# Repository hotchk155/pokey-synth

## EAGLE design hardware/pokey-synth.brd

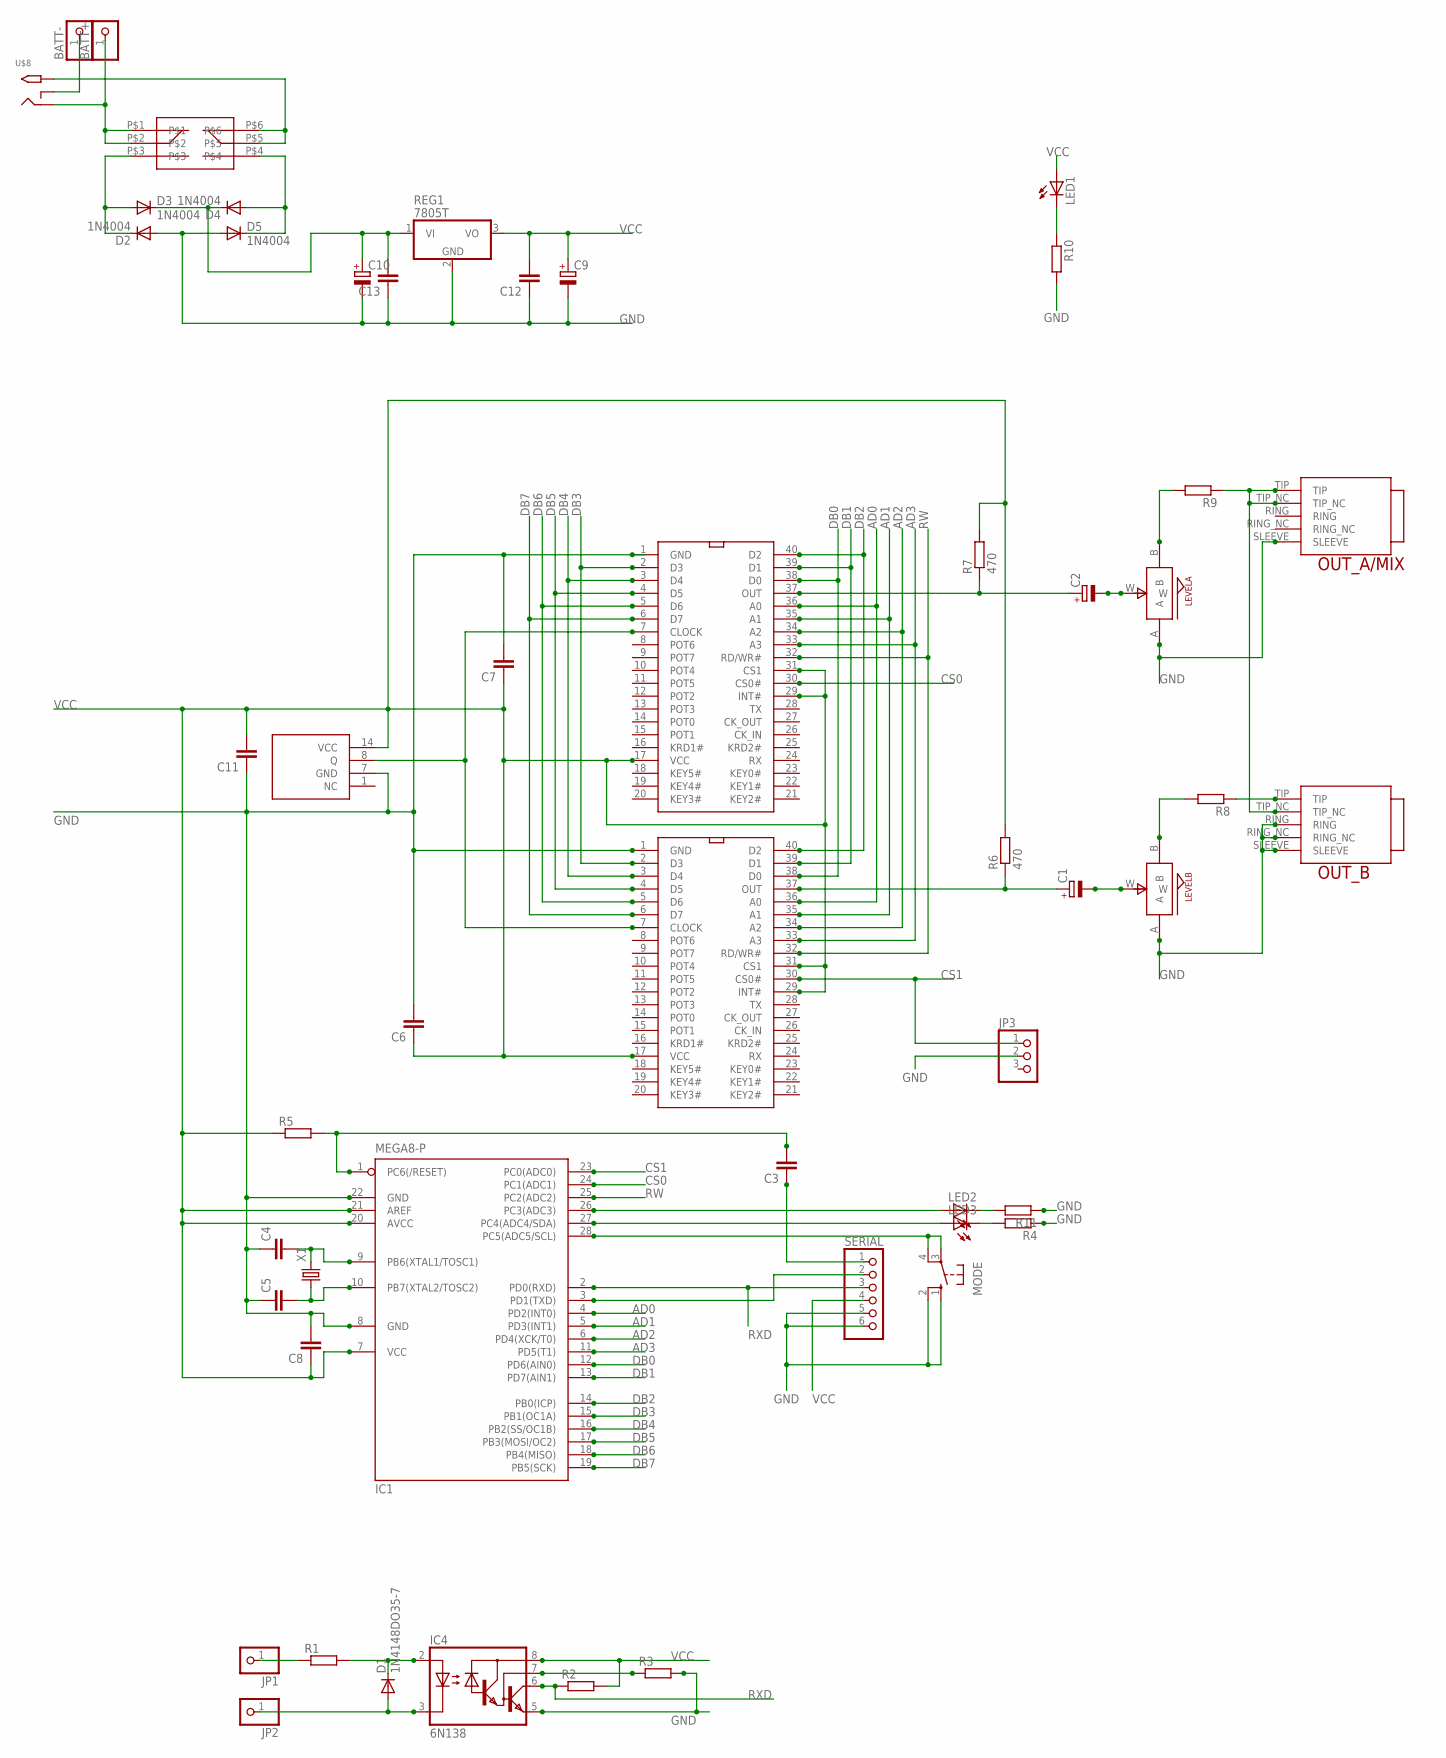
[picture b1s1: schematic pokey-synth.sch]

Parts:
BATT+: PINHD-1X1; 1X01
BATT-: PINHD-1X1; 1X01
C1, C2, C9, C10: CPOL-EUE2-5; E2-5
C3, C4, C5, C6, C7, C8, C11, C12, C13: C-EU025-024X044; C025-024X044
D1: 1N4148DO35-7; DO35-7
D2, D3, D4, D5: 1N4004; DO-VERT
IC1: MEGA8-P; DIL28-3
IC2, IC3: POKEYDIP40; DIL40
IC4: 6N138; DIL08
JP1, JP2: PINHD-1X1; 1X01
JP3: PINHD-1X3; 1X03
LED1, LED2, LED3: LED3MM
LEVELA: ALPS_POT_SMALL; SMALL_ALPS_POT
LEVELB: ALPS_POT_SMALL; SMALL_ALPS_POT
MODE: 10-XX; B3F-10XX
OSC1: TTLOSC
OUT_A/MIX: TRUCONNECTJACK
OUT_B: TRUCONNECTJACK
R1, R2, R3, R4, R5, R8, R9, R10, R11: R-EU_0207/7; 0207/7
R6, R7: 470; 0207/7
REG1: 7805T; TO220H
SERIAL: HEADER-1X6; 1X06_OVAL
U$8: 2.1MMJACKTHM; PJ-102A
U$9: 2P2T_LATCHING
X1: CRYSTALHC49U-V; HC49U-V

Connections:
AD0: IC1.4 (PD2(INT0)), IC2.36 (A0), IC3.36 (A0)
AD1: IC1.5 (PD3(INT1)), IC2.35 (A1), IC3.35 (A1)
AD2: IC1.6 (PD4(XCK/T0)), IC2.34 (A2), IC3.34 (A2)
AD3: IC1.11 (PD5(T1)), IC2.33 (A3), IC3.33 (A3)
CS0: IC1.24 (PC1(ADC1)), IC2.30 (CS0#)
CS1: IC1.23 (PC0(ADC0)), IC3.30 (CS0#), JP3.1
DB0: IC1.12 (PD6(AIN0)), IC2.38 (D0), IC3.38 (D0)
DB1: IC1.13 (PD7(AIN1)), IC2.39 (D1), IC3.39 (D1)
DB2: IC1.14 (PB0(ICP)), IC2.40 (D2), IC3.40 (D2)
DB3: IC1.15 (PB1(OC1A)), IC2.2 (D3), IC3.2 (D3)
DB4: IC1.16 (PB2(SS/OC1B)), IC2.3 (D4), IC3.3 (D4)
DB5: IC1.17 (PB3(MOSI/OC2)), IC2.4 (D5), IC3.4 (D5)
DB6: IC1.18 (PB4(MISO)), IC2.5 (D6), IC3.5 (D6)
DB7: IC1.19 (PB5(SCK)), IC2.6 (D7), IC3.6 (D7)
GND: C4.1, C5.1, C6.2, C7.2, C8.2, C9.-, C10.-, C11.1, C12.1, C13.1, D2.A, D5.A, IC1.8 (GND), IC1.22 (GND), IC2.1 (GND), IC3.1 (GND), IC4.5 (GND), JP3.2, LEVELA.A, LEVELB.A, MODE.1 (S), MODE.2 (S1), OSC1.7 (GND), OUT_A/MIX.SLEEVE, OUT_B.RING, OUT_B.RING_NC, OUT_B.SLEEVE, R3.2, R4.1, R10.2, R11.1, REG1.2 (GND), SERIAL.5, SERIAL.6
unnamed: C4.2, IC1.9 (PB6(XTAL1/TOSC1)), X1.2
unnamed: C5.2, IC1.10 (PB7(XTAL2/TOSC2)), X1.1
unnamed: C2.-, LEVELA.W
unnamed: LEVELA.B, R9.2
unnamed: OUT_A/MIX.TIP, OUT_A/MIX.TIP_NC, OUT_B.TIP_NC, R9.1
unnamed: C1.-, LEVELB.W
unnamed: JP1.1, R1.1
unnamed: LEVELB.B, R8.2
unnamed: OUT_B.TIP, R8.1
unnamed: IC2.7 (CLOCK), IC3.7 (CLOCK), OSC1.8 (Q)
unnamed: C2.+, IC2.37 (OUT), R7.1
unnamed: C1.+, IC3.37 (OUT), R6.1
unnamed: D1.C, IC4.2 (A), R1.2
unnamed: D1.A, IC4.3 (C), JP2.1
unnamed: BATT+.1, U$8.RING, U$9.P$1, U$9.P$2
unnamed: IC4.7 (VB), R3.1
unnamed: U$8.TIP, U$9.P$5, U$9.P$6
unnamed: C3.2, IC1.1 (PC6(/RESET)), R5.2
unnamed: BATT-.1, U$8.RING_SW
unnamed: C3.1, SERIAL.1
unnamed: D2.C, D3.A, U$9.P$3
unnamed: D4.A, D5.C, U$9.P$4
unnamed: C10.+, C13.2, D3.C, D4.C, REG1.1 (VI)
unnamed: LED1.K (C), R10.1
unnamed: IC1.26 (PC3(ADC3)), LED2.A
unnamed: LED2.K (C), R11.2
unnamed: IC1.28 (PC5(ADC5/SCL)), MODE.3, MODE.4 (P1)
unnamed: IC1.27 (PC4(ADC4/SDA)), LED3.A
unnamed: LED3.K (C), R4.2
RW: IC1.25 (PC2(ADC2)), IC2.32 (RD/WR#), IC3.32 (RD/WR#)
RXD: IC1.2 (PD0(RXD)), IC4.6 (VO), R2.1, SERIAL.3
TXD: IC1.3 (PD1(TXD)), SERIAL.2
VCC: C6.1, C7.1, C8.1, C9.+, C11.2, C12.2, IC1.7 (VCC), IC1.20 (AVCC), IC1.21 (AREF), IC2.17 (VCC), IC2.29 (INT#), IC2.31 (CS1), IC3.17 (VCC), IC3.29 (INT#), IC3.31 (CS1), IC4.8 (VCC), LED1.A, OSC1.14 (VCC), R2.2, R5.1, R6.2, R7.2, REG1.3 (VO), SERIAL.4

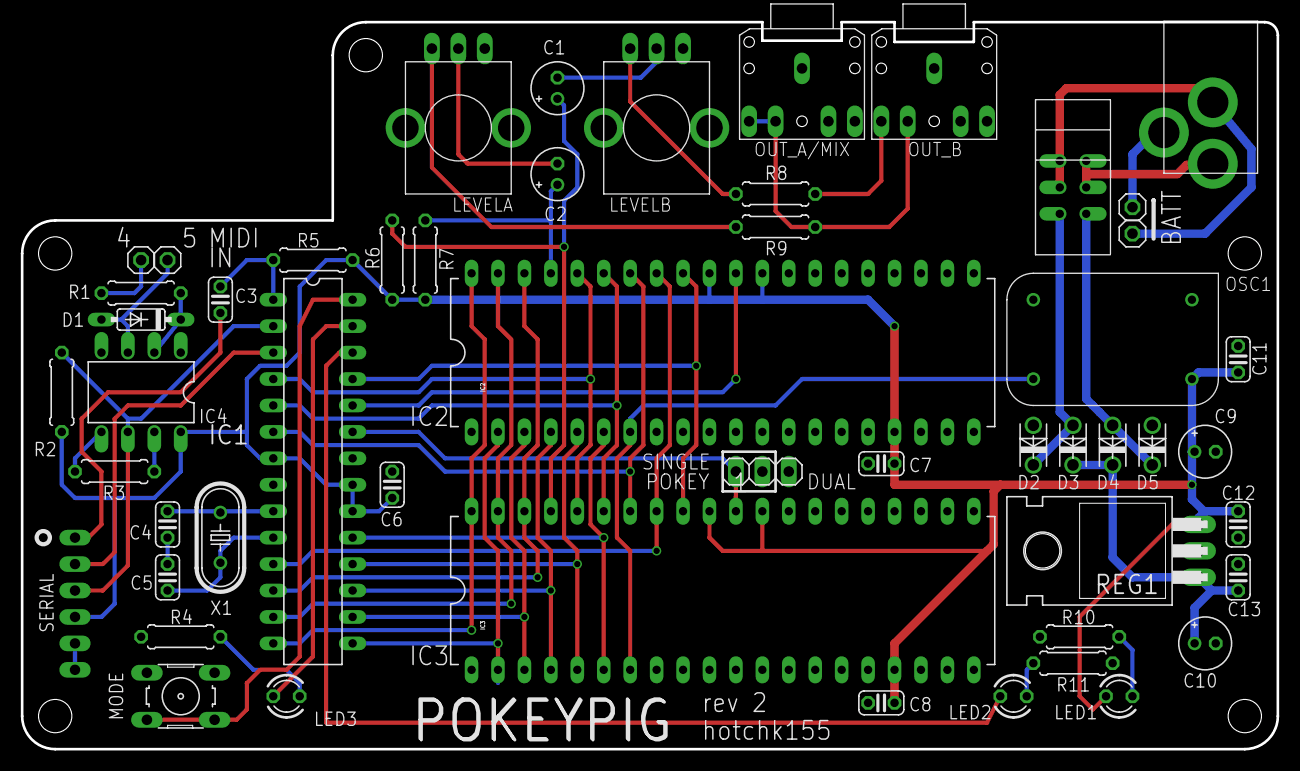
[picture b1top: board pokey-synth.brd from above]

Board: 2 copper layers, 120.7 x 69.8 mm, 52 parts (0 on the bottom side), 48 nets.

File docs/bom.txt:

POKEYPIG 
--------
C1, C2			100UF ELECTROLYTIC CAPACITOR
C3, C6, C7, 		100NF CERAMIC CAPACITOR
C8, C11, C12, C13 	100NF CERAMIC CAPACITOR
C4, C5                  33PF CERAMIC CAPACITOR
C9, C10			4U7
D1        		1N4148 SMALL SIGNAL DIODE 
D2, D3, D4, D5		1N4004 RECTIFIER DIODE
IC1       		ATMEGA328P DIP-28 (SOCKETED)
IC2, IC3       		CO12294 'POKEY' DIP-40 (SOCKETED)
IC4       		6N138 OPTO ISOLATOR
X1                      16MHZ CRYSTAL
REG1      		7805 REGULATOR TO-220
LED1, LED2, LED3        3MM LED RECTANGULAR             
OSC1      		2MHZ TTL-OUTPUT CRYSTAL OSCILLATOR

R1			220 OHM      
R6, R7			470 OHM           
R4, R10, R11		1K OHM                       
R2, R3			1.5K OHM                       
R5			10K OHM
R8, R9      		100K OHM

LEVELA, LEVELB		MINIATURE (9MM) PCB MOUNT POT 100K OHM WITH KNOB

POWER SWITCH       	2P2T LATCHING PUSH BUTTON SWITCH + CAP
MODE                    PCB MOUNT VERTICAL MOMENTARY SWITCH + CAP

SERIAL	  		6 WAY RIGHT ANGLE SIL HEADER
JP3			3 PIN SIL HEADER WITH 2 PIN JUMPER        
POWER SOCKET	  	2.1MM DC JACK (SWITCHING)
MIDI IN 		PANEL MOUNT 5 PIN DIN SOCKET



(10 OFF) M3 x 8MM ALLEN HEAD MACHINE SCREW
(4 OFF) M3 X 12MM ALLEN HEAD MACHINE SCREW
(7 OFF) M3 NUT

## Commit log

2015-05-29 :circus_tent: Added .gitattributes & .gitignore files
2015-05-29 tweaks
2015-05-29 pcb ready
2015-06-21 evelopes / trem / vibrato
2015-06-21 unison and detune
2015-06-22 progress
2015-06-24 stuff
2015-06-26 moving parts
2015-06-30 more stuff
2015-07-03 blood sweat tears
2015-07-03 stuff an nonsens
2015-07-03 changes to CC numbers
2015-07-03 changes to ccs
2015-07-20 panel
2015-08-24 panel update
2015-08-30 add jumper
2015-09-04 ready for pcb rev2
2015-09-29 new pcb layout
2015-11-29 work in progress
2015-11-30 in progress
2015-12-05 u guessed it - more stuff
2015-12-14 current panel
2016-03-14 BOM / single POKEY fascia
